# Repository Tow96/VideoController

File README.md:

# Video Controller Surface

Simple surface for video editing utilizing a Teensy 2.0 It's main purpose is to be utilized with the program 
Adobe Premiere Pro. However, thanks to the Teensy's HID interface, can also be utilized as a multipurpose 
Macro pad.

This surface has 12 buttons, a main central knob, and 3 secondary knobs. The four knobs also have buttons.

This project is heavily based by Zack-Freedman's [Big-Wheel](https://github.com/ZackFreedman/Big-Wheel) 
project.

## Repository structure
The repository is divided in four subfolders, each containing a different part of the project. Further 
documentation can be found inside these folders.

1. [**Assembly**](/Assembly) - This folder contains the files that make up the physical device. They are 
available in .SLDPRT and .STL formats.

2. [**Firmware**](/Firmware) - This folder contains the Firmware utilized by the device. It is built in 
platform.io and uses the [Teensyduino](https://www.pjrc.com/teensy/td_download.html) library.

3. [**Schematics**](/Schematics) - This folder contains the wiring diagrams, as well as the elements to 
manufacture a PCB for it.

4. [**Shortcut-Profiles**](/Shortcut-Profiles) - This folder contains .kys files for Adobe Premiere.

## Future improvements
The improvements are separated by category inside the documentation for each folder.

## Credits
- Jose Tow [[@Tow96](https://github.com/Tow96)]

Original idea from: Zack Freedman ([github](https://github.com/ZackFreedman), 
[youtube](https://www.youtube.com/channel/UCUW49KGPezggFi0PGyDvcvg))

## License
This project is licensed under [MIT license](/LICENSE) as I believe in open-source, specially when basing 
your project from another.

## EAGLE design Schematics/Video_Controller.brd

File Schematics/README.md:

# Schematics
This folder contains the wiring diagrams, as well as the elements to manufacture a PCB for it.

The files are in EAGLE CAD format and also the gbr files are available to manufacture a PCB out of it.

**Warning:** The PCB has tolerances to fit inside the body of the device, and test prints have 
been made to check if the components fit. However a proper PCB hasn't been manufatured to test

## Teensy pins
The pins to which each component is wired can be changed on the [pins.h](../Firmware/src/pins.h) 
file. The default connections are:

Wire      | Pin
--------- | ---
Row A     | 5
Row B     | 6
Row C     | 16
Row D     | 15
Col 1     | 17
Col 2     | 18
Col 3     | 3
Col 4     | 4
TopKnob A | 8
TopKnob B | 7
MidKnob A | 10
MidKnob B | 9
BotKnob A | 13
BotKnob B | 14
Wheel A   | 11
Wheel B   | 12

## Hand soldering
The case is also designed to be hand soldered instead of using a pcb. Here is the name of each button and knob matching the schematics.

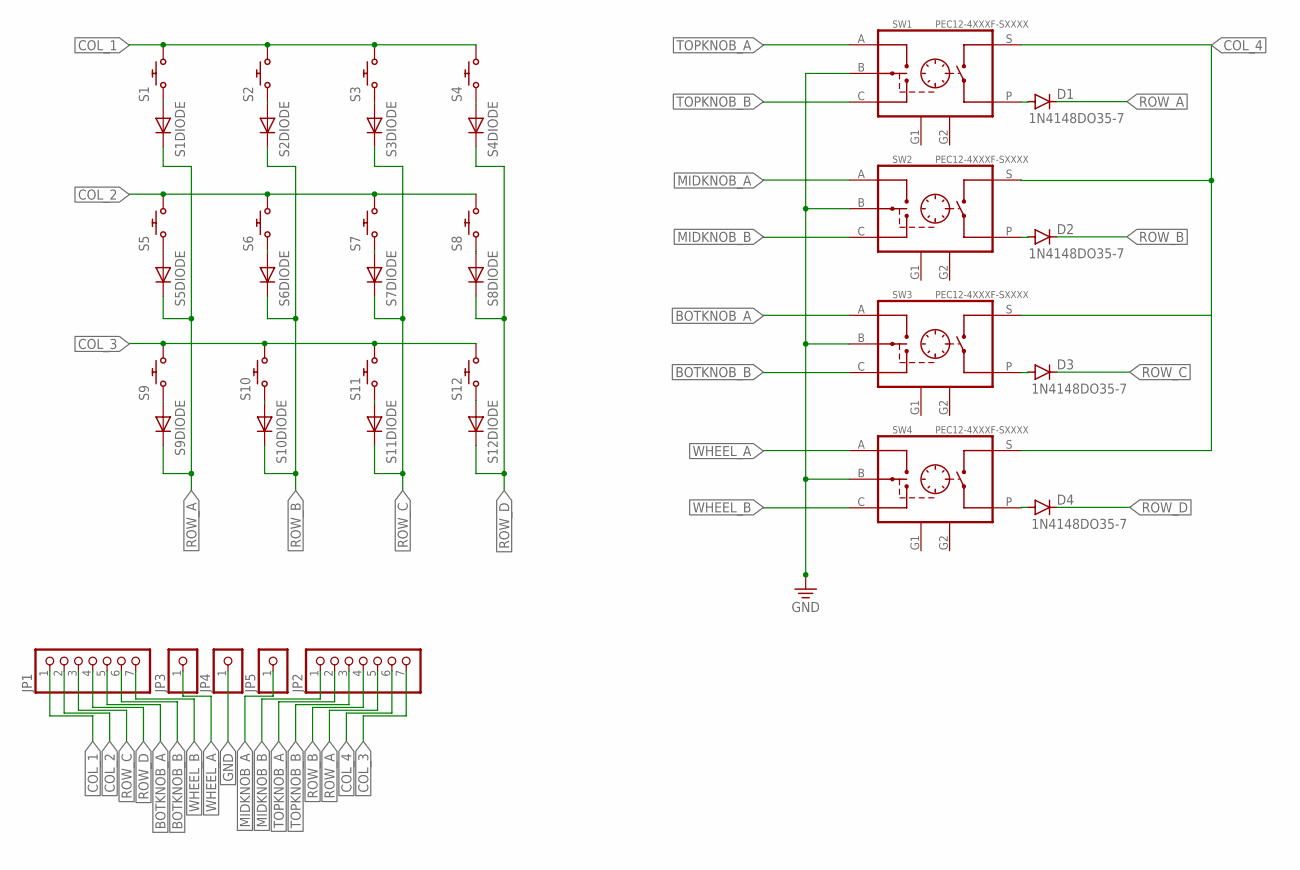
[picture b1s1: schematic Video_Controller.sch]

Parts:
D1, D2, D3, D4: 1N4148DO35-7; DO35-7
JP1, JP2: PINHD-1X7; 1X07
JP3, JP4, JP5: PINHD-1X1; 1X01
S1, S2, S3, S4, S5, S6, S7, S8, S9, S10, S11, S12: CHERY_MX_DIODE; CHERRY_MX_DIODE
SW1, SW2, SW3, SW4: PEC12-4XXXF-SXXXX; PEC12-4XXX

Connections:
BOTKNOB_A: JP1.5, SW3.A
BOTKNOB_B: JP1.6, SW3.C
COL_1: JP1.1, S1.S2 (2), S2.S2 (2), S3.S2 (2), S4.S2 (2)
COL_2: JP1.2, S5.S2 (2), S6.S2 (2), S7.S2 (2), S8.S2 (2)
COL_3: JP2.7, S9.S2 (2), S10.S2 (2), S11.S2 (2), S12.S2 (2)
COL_4: JP2.6, SW1.S
GND: JP4.1, SW1.B, SW2.B, SW3.B, SW4.B
MIDKNOB_A: JP5.1, SW2.A
MIDKNOB_B: JP2.1, SW2.C
unnamed: S1.D1 (A), S1.S1 (1)
unnamed: S2.D1 (A), S2.S1 (1)
unnamed: S3.D1 (A), S3.S1 (1)
unnamed: S4.D1 (A), S4.S1 (1)
unnamed: D1.A, SW1.P
unnamed: D2.A, SW2.P
unnamed: D3.A, SW3.P
unnamed: D4.A, SW4.P
unnamed: S5.D1 (A), S5.S1 (1)
unnamed: S6.D1 (A), S6.S1 (1)
unnamed: S7.D1 (A), S7.S1 (1)
unnamed: S8.D1 (A), S8.S1 (1)
unnamed: S9.D1 (A), S9.S1 (1)
unnamed: S11.D1 (A), S11.S1 (1)
unnamed: S10.D1 (A), S10.S1 (1)
unnamed: SW2.S, SW3.S, SW4.S
unnamed: S12.D1 (A), S12.S1 (1)
ROW_A: D1.C, JP2.5, S1.D2 (C), S5.D2 (C), S9.D2 (C)
ROW_B: D2.C, JP2.4, S2.D2 (C), S6.D2 (C), S10.D2 (C)
ROW_C: D3.C, JP1.3, S3.D2 (C), S7.D2 (C), S11.D2 (C)
ROW_D: D4.C, JP1.4, S4.D2 (C), S8.D2 (C), S12.D2 (C)
TOPKNOB_A: JP2.2, SW1.A
TOPKNOB_B: JP2.3, SW1.C
WHEEL_A: JP3.1, SW4.A
WHEEL_B: JP1.7, SW4.C

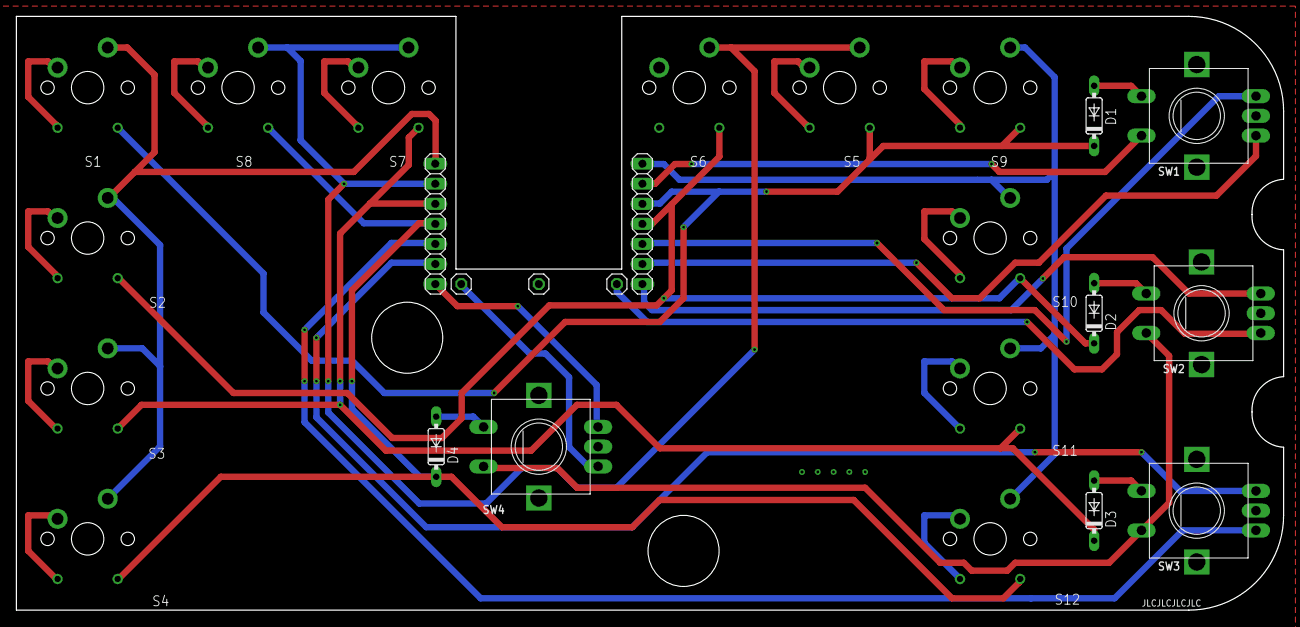
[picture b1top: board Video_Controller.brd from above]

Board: 2 copper layers, 160.5 x 75.2 mm, 25 parts (0 on the bottom side), 34 nets.

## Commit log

2021-04-10 v1.0
    Version 1.0 of the Video Controller
2021-05-08 Added .gitignore to ignore Solidworks temporary files
2021-05-09 added conversion to atmega32u4
    The USBCore.cpp file is there to override the base file and remove the Serial Port
2021-05-09 Moved the header files to /include
2021-05-09 Updated the code to arduino
    The Action queue is missing

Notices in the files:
README.md:
License: MIT
